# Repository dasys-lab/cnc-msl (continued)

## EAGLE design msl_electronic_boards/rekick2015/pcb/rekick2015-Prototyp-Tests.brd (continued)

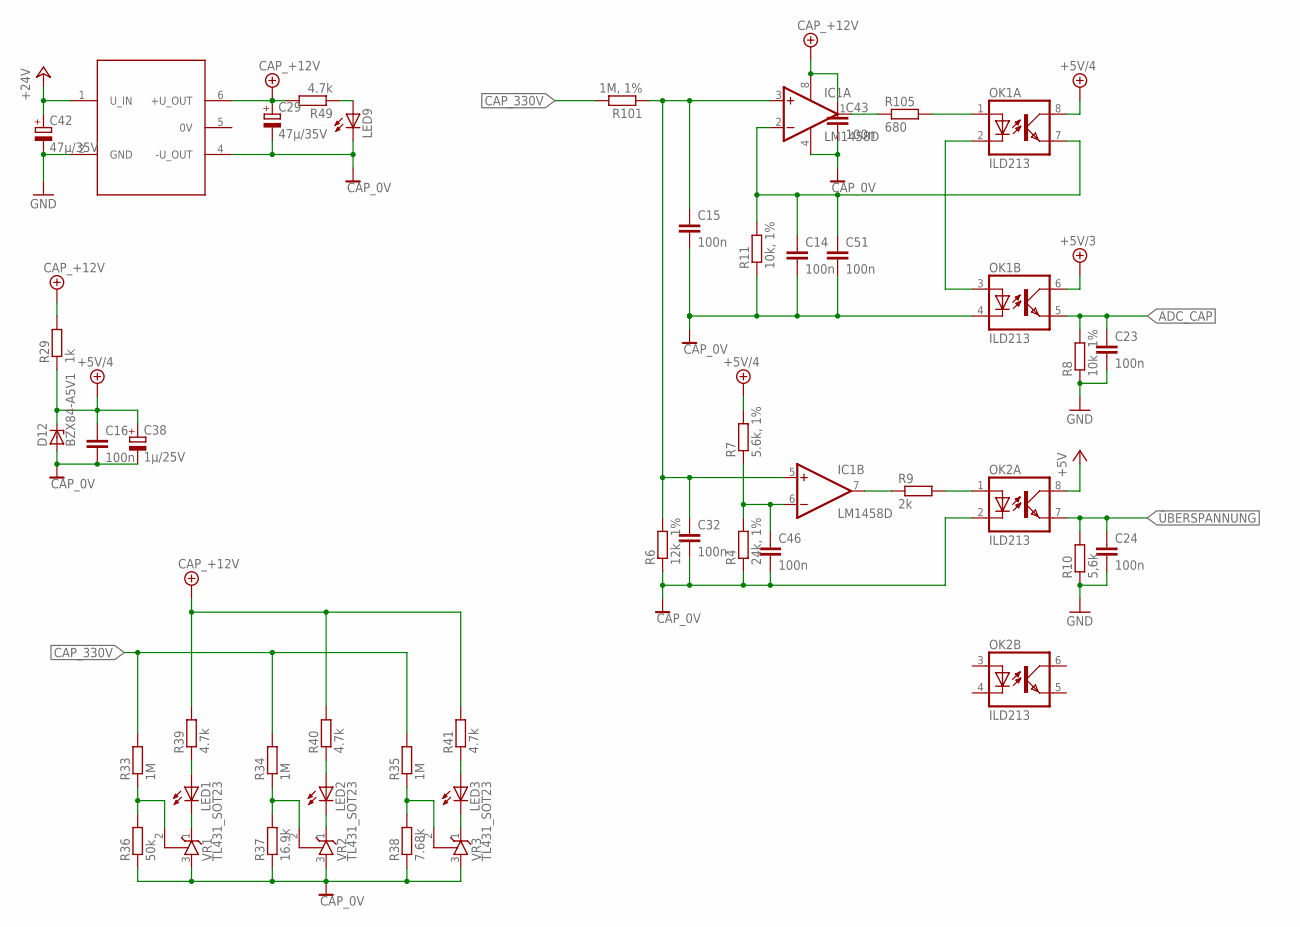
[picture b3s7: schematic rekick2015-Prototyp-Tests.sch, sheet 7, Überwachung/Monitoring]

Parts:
C14, C15, C16, C23, C24, C32, C43, C46, C51: 100n; C0603
C29, C42: 47µ/35V; PANASONIC_D
C38: 1µ/25V; SMC_A
D12: BZX84-A5V1; TO236
IC1: LM1458D; SO08
LED1, LED2, LED3, LED9: LEDCHIP-LED0805; CHIP-LED0805
OK1, OK2: ILD213; SOIC08
R4: 24k, 1%; R0805
R6: 12k, 1%; R0805
R7: 5.6k, 1%; R0805
R8, R11: 10k, 1%; R0805
R9: 2k; R0805
R10: 5,6k; R0805
R29: 1k; R0805
R33, R34, R35: 1M; R2512
R36: 50k; R0805
R37: 16.9k; R0805
R38: 7.68k; R0805
R39, R40, R41, R49: 4.7k; R0805
R101: 1M, 1%; R2512
R105: 680; R0805
U$4: TMH-D
VR1, VR2, VR3: TL431_SOT23; SOT23

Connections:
+5V: OK2.8 (COL); also elsewhere on the board
+5V/3: OK1.6 (COL); also elsewhere on the board
+5V/4: C16.1, C38.+, D12.C, OK1.8 (COL), R7.2, R29.1
+24V: C42.+, U$4.1 (U_IN); also elsewhere on the board
ADC_CAP: C23.1, OK1.5 (EMIT), R8.2; also elsewhere on the board
CAP_0V: C14.2, C15.2, C16.2, C29.-, C32.2, C38.-, C43.2, C46.2, C51.2, D12.A, IC1.4 (V-), LED9.C, OK1.4 (C), OK2.2 (C), R4.1, R6.1, R11.1, R36.1, R37.1, R38.1, U$4.4 (-U_OUT), VR1.3 (A), VR2.3 (A), VR3.3 (A); also elsewhere on the board
CAP_330V: R33.2, R34.2, R35.2, R101.2; also elsewhere on the board
CAP_+12V: C29.+, C43.1, IC1.8 (V+), R29.2, R39.2, R40.2, R41.2, R49.2, U$4.6 (+U_OUT); also elsewhere on the board
GND: C23.2, C24.2, C42.-, R8.1, R10.1, U$4.2 (GND); also elsewhere on the board
unnamed: LED1.C, VR1.1 (C)
unnamed: R33.1, R36.2, VR1.2 (R)
unnamed: IC1.1 (OUT), R105.1
unnamed: C14.1, C51.1, IC1.2 (-IN), OK1.7 (EMIT), R11.2
unnamed: C15.1, C32.1, IC1.3 (+IN), IC1.5 (+IN), R6.2, R101.1
unnamed: OK1.1 (A), R105.2
unnamed: OK1.2 (C), OK1.3 (A)
unnamed: IC1.7 (OUT), R9.1
unnamed: C46.1, IC1.6 (-IN), R4.2, R7.1
unnamed: OK2.1 (A), R9.2
unnamed: R34.1, R37.2, VR2.2 (R)
unnamed: R35.1, R38.2, VR3.2 (R)
unnamed: LED2.C, VR2.1 (C)
unnamed: LED3.C, VR3.1 (C)
unnamed: LED1.A, R39.1
unnamed: LED2.A, R40.1
unnamed: LED3.A, R41.1
unnamed: LED9.A, R49.1
ÜBERSPANNUNG: C24.1, OK2.7 (EMIT), R10.2; also elsewhere on the board

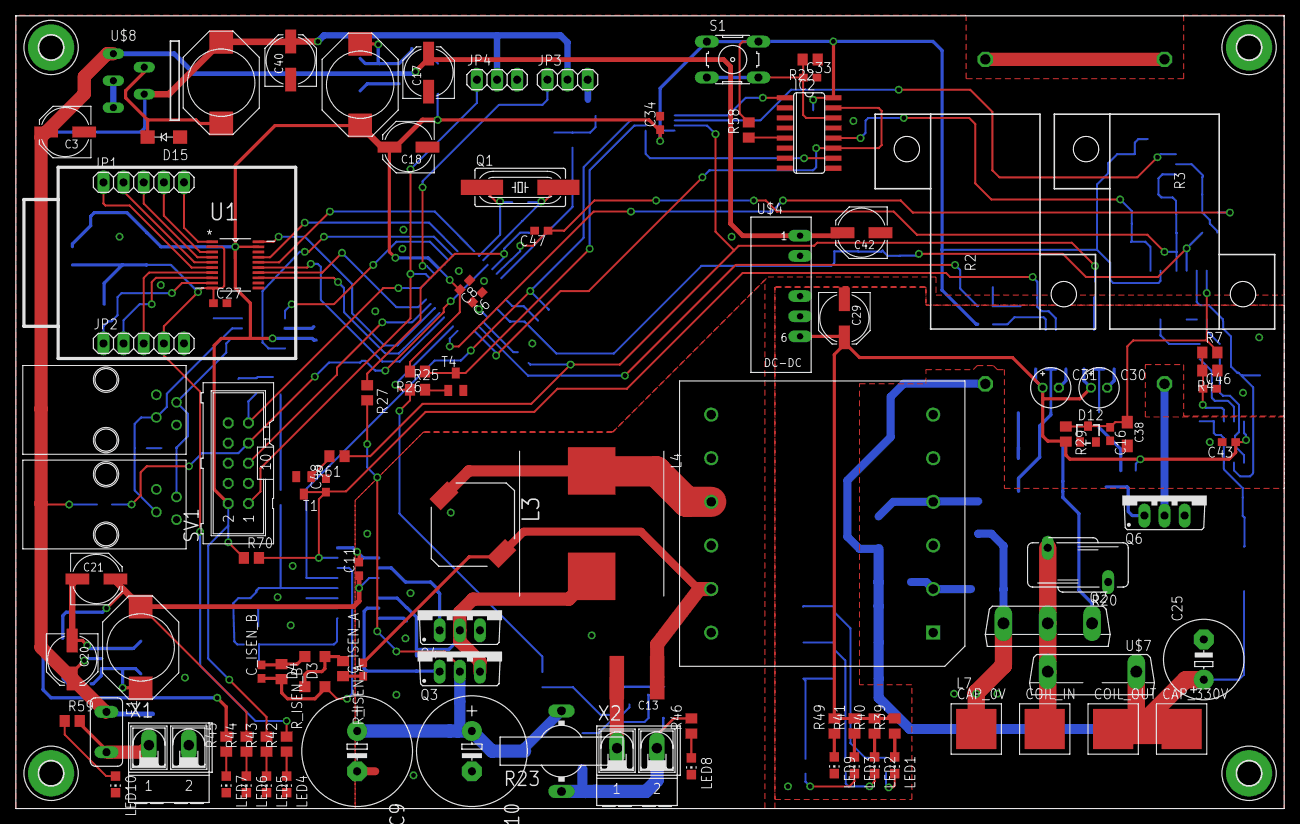
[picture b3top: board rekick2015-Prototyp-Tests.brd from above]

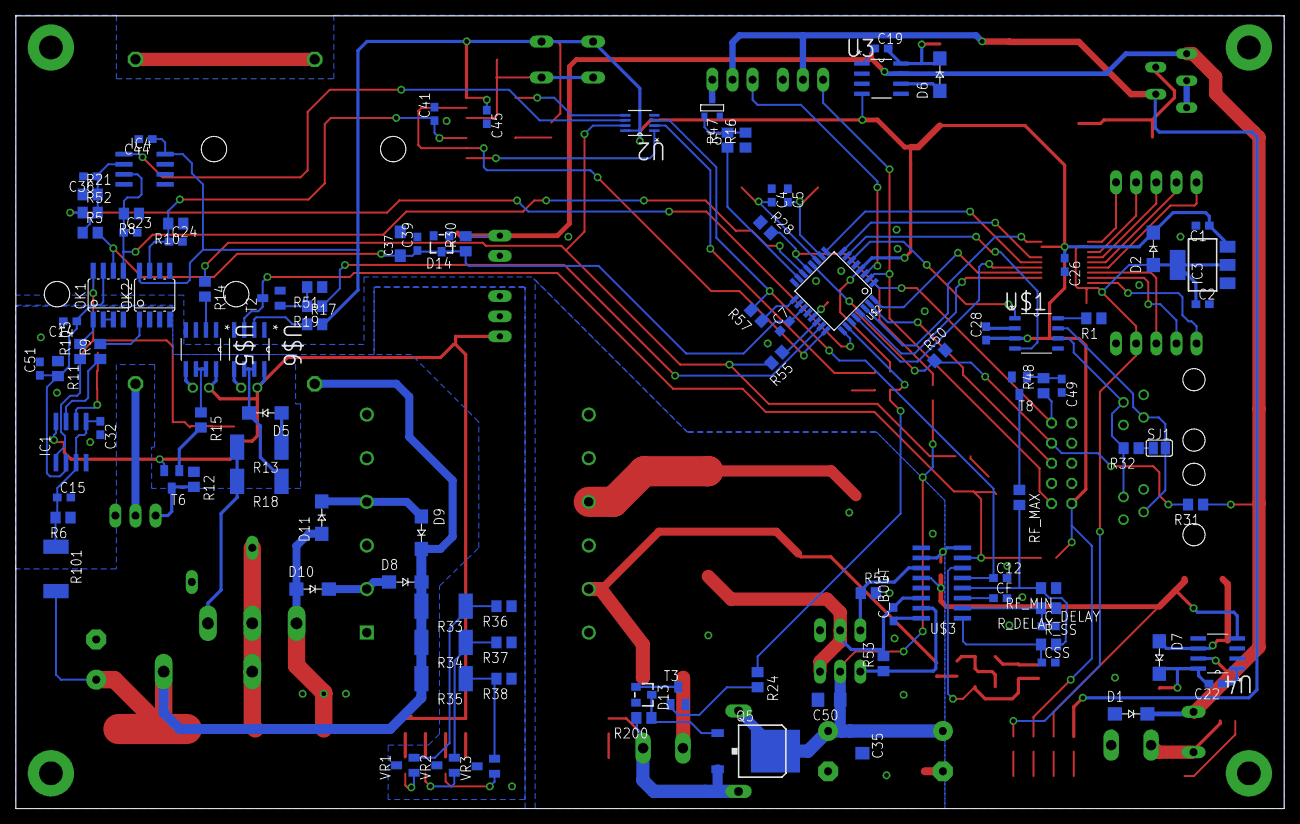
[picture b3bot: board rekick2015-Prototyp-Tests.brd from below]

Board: 2 copper layers, 160.0 x 100.0 mm, 211 parts (106 on the bottom side), 128 nets.

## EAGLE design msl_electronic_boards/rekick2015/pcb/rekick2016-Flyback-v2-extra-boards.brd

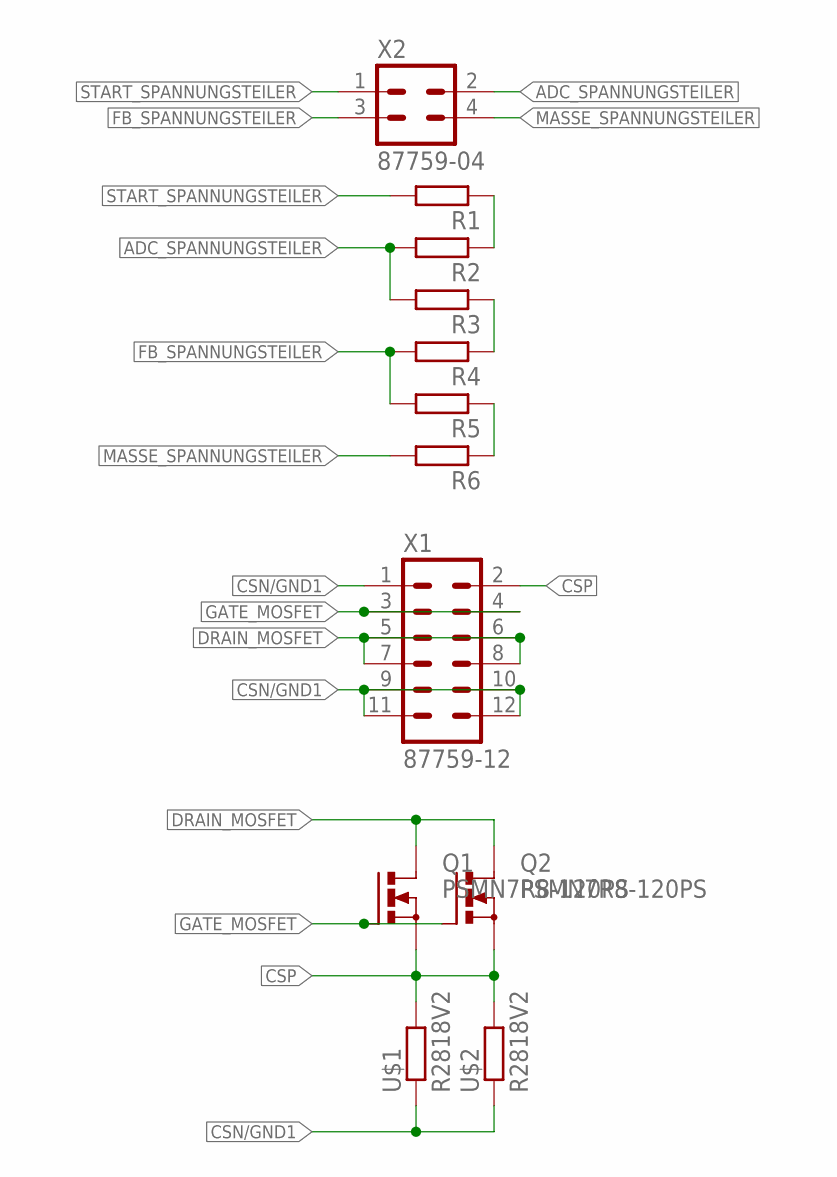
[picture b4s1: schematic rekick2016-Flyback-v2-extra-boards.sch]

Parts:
Q1, Q2: PSMN7R8-120PS; TO220BV
R1, R2, R3, R4, R5, R6: R-EU_R0805; R0805
U$1, U$2: R2818V2; R2818
X1: 87759-12
X2: 87759-04

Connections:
ADC_SPANNUNGSTEILER: R2.2, R3.2, X2.2
CSN/GND1: U$1.1, U$2.1, X1.1, X1.9, X1.10, X1.11, X1.12
CSP: Q1.S, Q2.S, U$1.2, U$2.2, X1.2
DRAIN_MOSFET: Q1.D, Q2.D, X1.5, X1.6, X1.7, X1.8
FB_SPANNUNGSTEILER: R4.2, R5.2, X2.3
GATE_MOSFET: Q1.G, Q2.G, X1.3, X1.4
MASSE_SPANNUNGSTEILER: R6.2, X2.4
unnamed: R1.1, R2.1
unnamed: R3.1, R4.1
unnamed: R5.1, R6.1
START_SPANNUNGSTEILER: R1.2, X2.1

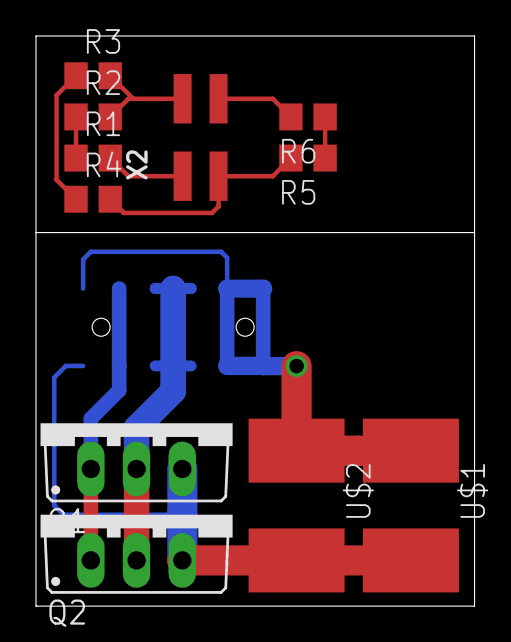
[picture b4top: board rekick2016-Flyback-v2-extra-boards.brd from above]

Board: 2 copper layers, 24.4 x 31.7 mm, 12 parts (1 on the bottom side), 11 nets.

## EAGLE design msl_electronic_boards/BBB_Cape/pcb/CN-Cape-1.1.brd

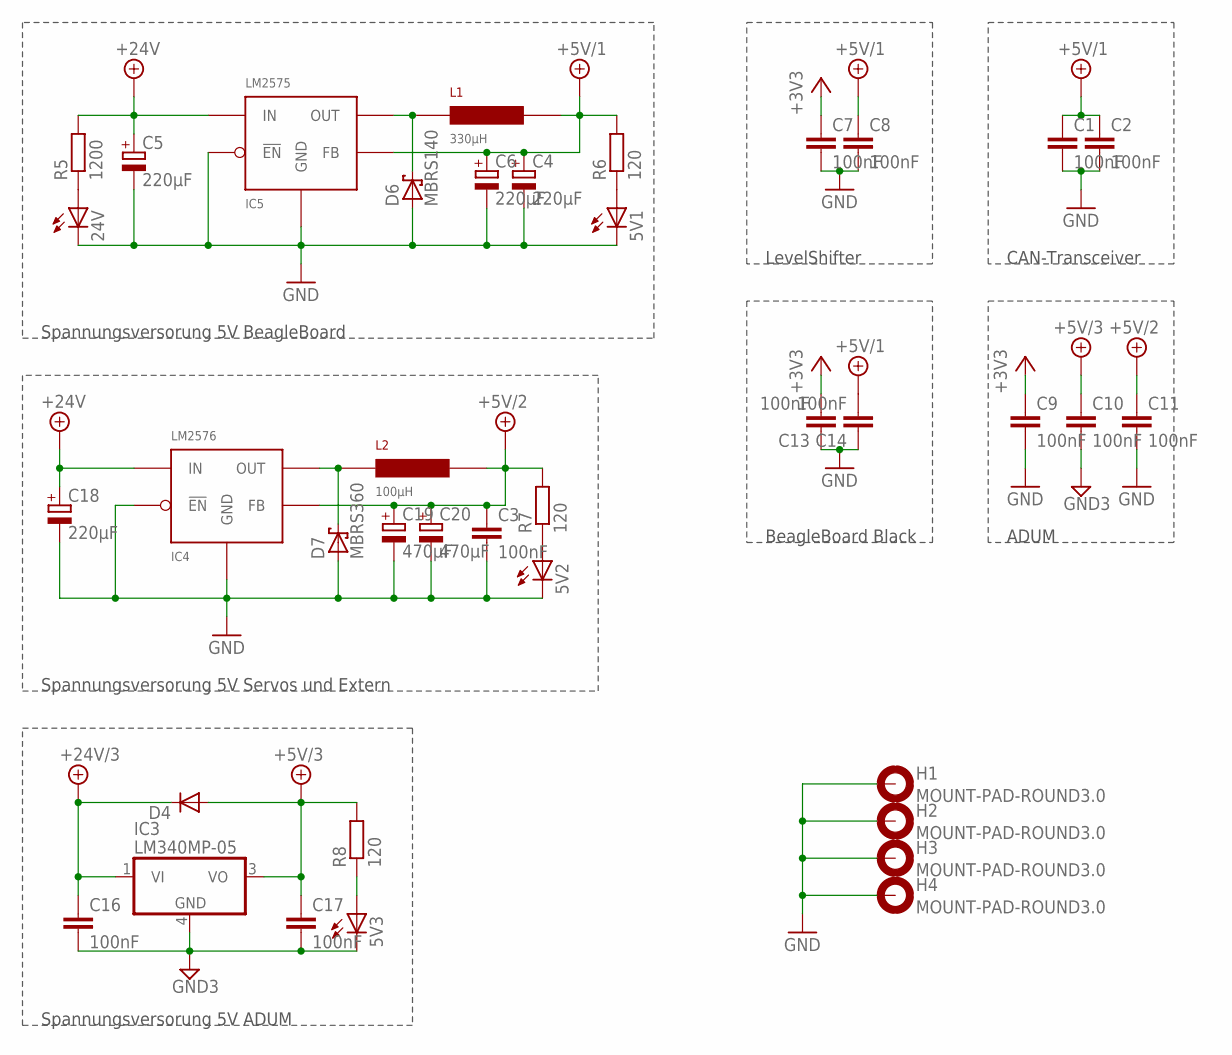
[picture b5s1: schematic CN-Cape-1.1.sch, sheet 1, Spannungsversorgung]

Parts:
5V1, 5V2, 5V3, 24V: LEDCHIP-LED0603; CHIP-LED0603
C1, C2, C3, C7, C8, C9, C10, C11, C13, C14, C16, C17: 100nF; C0603
C4, C6: 220µF; E2,5-6
C5, C18: 220µF; E3,5-8
C19, C20: 470µF; E3,5-8
D4: DIODE-SOD123; SOD123
D6: MBRS140; SMB
D7: MBRS360; SMC
H1, H2, H3, H4: MOUNT-PAD-ROUND3.0; 3,0-PAD
IC3: LM340MP-05; SOT223
IC4: LM2576; TO220-5_STAGGERED
IC5: LM2575; TO220-5_STAGGERED
L1: 330µH; PISR
L2: 100µH; PISR
R5: 1200; R0805
R6, R7, R8: 120; R0805

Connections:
+3V3: C7.1, C9.1, C13.2; also elsewhere on the board
+5V/1: C1.1, C2.1, C4.+, C6.+, C8.1, C14.2, IC5.FB, L1.P$2, R6.2; also elsewhere on the board
+5V/2: C3.1, C11.1, C19.+, C20.+, IC4.FB, L2.P$2, R7.2; also elsewhere on the board
+5V/3: C10.1, C17.1, D4.A, IC3.3 (VO), R8.2; also elsewhere on the board
+24V: C5.+, C18.+, IC4.IN, IC5.IN, R5.2; also elsewhere on the board
+24V/3: C16.1, D4.C, IC3.1 (VI); also elsewhere on the board
GND: 5V1.C, 5V2.C, 24V.C, C1.2, C2.2, C3.2, C4.-, C5.-, C6.-, C7.2, C8.2, C9.2, C11.2, C13.1, C14.1, C18.-, C19.-, C20.-, D6.A, D7.A, H1.B3,0, H2.B3,0, H3.B3,0, H4.B3,0, IC4.!EN, IC4.GND, IC5.!EN, IC5.GND; also elsewhere on the board
GND3: 5V3.C, C10.2, C16.2, C17.2, IC3.4 (GND); also elsewhere on the board
unnamed: 24V.A, R5.1
unnamed: 5V1.A, R6.1
unnamed: 5V2.A, R7.1
unnamed: D6.C, IC5.OUT, L1.P$1
unnamed: D7.C, IC4.OUT, L2.P$1
unnamed: 5V3.A, R8.1

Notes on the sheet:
LevelShifter
CAN-Transceiver
BeagleBoard Black
Spannungsversorung 5V BeagleBoard
Spannungsversorung 5V Servos und Extern
Spannungsversorung 5V ADUM
ADUM

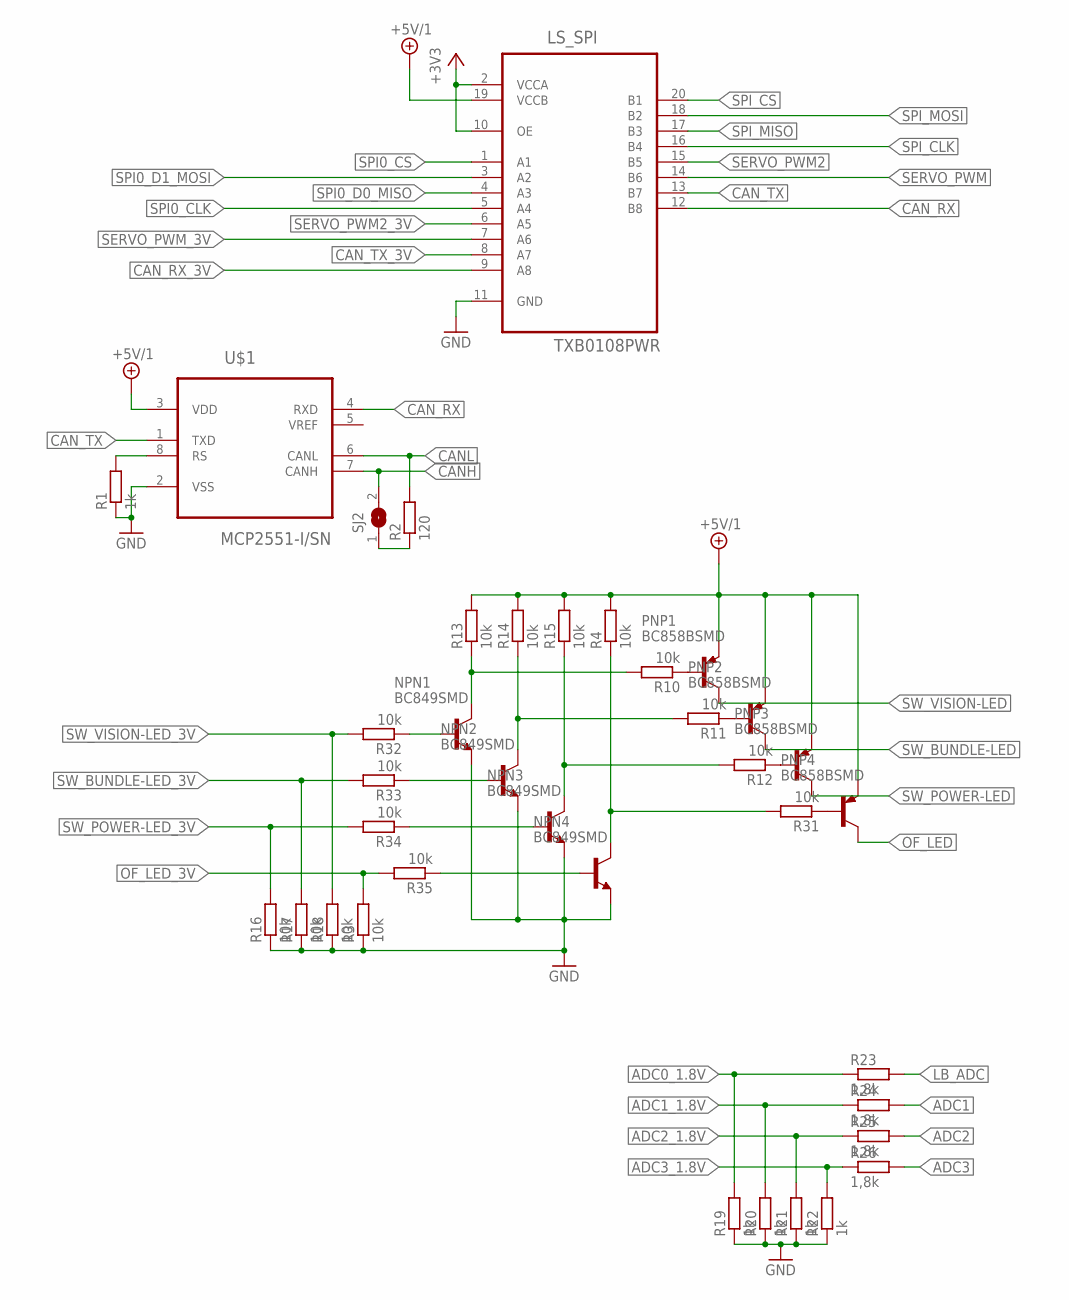
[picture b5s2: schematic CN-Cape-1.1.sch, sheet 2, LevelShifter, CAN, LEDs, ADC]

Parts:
LS_SPI: TXB0108PWR; SOP65P640X120-20N
NPN1, NPN2, NPN3, NPN4: BC849SMD; SOT23-BEC
PNP1, PNP2, PNP3, PNP4: BC858BSMD; SOT23-BEC
R1, R19, R20, R21, R22: 1k; R0805
R2: 120; R0805
R3, R4, R10, R11, R12, R13, R14, R15, R16, R17, R18, R31, R32, R33, R34, R35: 10k; R0805
R23, R24, R25, R26: 1,8k; R0805
SJ2: SJ
U$1: MCP2551-I/SN; SOIC127P600X175-8N

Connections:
+3V3: LS_SPI.2 (VCCA), LS_SPI.10 (OE); also elsewhere on the board
+5V/1: LS_SPI.19 (VCCB), PNP1.E, PNP2.E, PNP3.E, PNP4.E, R4.2, R13.2, R14.2, R15.2, U$1.3 (VDD); also elsewhere on the board
ADC0_1.8V: R19.2, R23.1; also elsewhere on the board
ADC1: R24.2; also elsewhere on the board
ADC1_1.8V: R20.2, R24.1; also elsewhere on the board
ADC2: R25.2; also elsewhere on the board
ADC2_1.8V: R21.2, R25.1; also elsewhere on the board
ADC3: R26.2; also elsewhere on the board
ADC3_1.8V: R22.2, R26.1; also elsewhere on the board
CANH: SJ2.2, U$1.7 (CANH); also elsewhere on the board
CANL: R2.2, U$1.6 (CANL); also elsewhere on the board
CAN_RX: LS_SPI.12 (B8), U$1.4 (RXD)
CAN_RX_3V: LS_SPI.9 (A8); also elsewhere on the board
CAN_TX: LS_SPI.13 (B7), U$1.1 (TXD)
CAN_TX_3V: LS_SPI.8 (A7); also elsewhere on the board
GND: LS_SPI.11 (GND), NPN1.E, NPN2.E, NPN3.E, NPN4.E, R1.1, R3.1, R16.1, R17.1, R18.1, R19.1, R20.1, R21.1, R22.1, U$1.2 (VSS); also elsewhere on the board
LB_ADC: R23.2; also elsewhere on the board
unnamed: NPN1.C, R10.2, R13.1
unnamed: NPN2.C, R11.2, R14.1
unnamed: NPN4.C, R4.1, R31.2
unnamed: NPN3.C, R12.2, R15.1
unnamed: R1.2, U$1.8 (RS)
unnamed: R2.1, SJ2.1
unnamed: PNP1.B, R10.1
unnamed: PNP2.B, R11.1
unnamed: PNP3.B, R12.1
unnamed: PNP4.B, R31.1
unnamed: NPN1.B, R32.1
unnamed: NPN2.B, R33.1
unnamed: NPN3.B, R34.1
unnamed: NPN4.B, R35.1
OF_LED: PNP4.C; also elsewhere on the board
OF_LED_3V: R3.2, R35.2; also elsewhere on the board
SERVO_PWM: LS_SPI.14 (B6); also elsewhere on the board
SERVO_PWM2: LS_SPI.15 (B5); also elsewhere on the board
SERVO_PWM2_3V: LS_SPI.6 (A5); also elsewhere on the board
SERVO_PWM_3V: LS_SPI.7 (A6); also elsewhere on the board
SPI0_CLK: LS_SPI.5 (A4); also elsewhere on the board
SPI0_CS: LS_SPI.1 (A1); also elsewhere on the board
SPI0_D0_MISO: LS_SPI.4 (A3); also elsewhere on the board
SPI0_D1_MOSI: LS_SPI.3 (A2); also elsewhere on the board
SPI_CLK: LS_SPI.16 (B4); also elsewhere on the board
SPI_CS: LS_SPI.20 (B1); also elsewhere on the board
SPI_MISO: LS_SPI.17 (B3); also elsewhere on the board
SPI_MOSI: LS_SPI.18 (B2); also elsewhere on the board
SW_BUNDLE-LED: PNP2.C; also elsewhere on the board
SW_BUNDLE-LED_3V: R17.2, R33.2; also elsewhere on the board
SW_POWER-LED: PNP3.C; also elsewhere on the board
SW_POWER-LED_3V: R16.2, R34.2; also elsewhere on the board
SW_VISION-LED: PNP1.C; also elsewhere on the board
SW_VISION-LED_3V: R18.2, R32.2; also elsewhere on the board

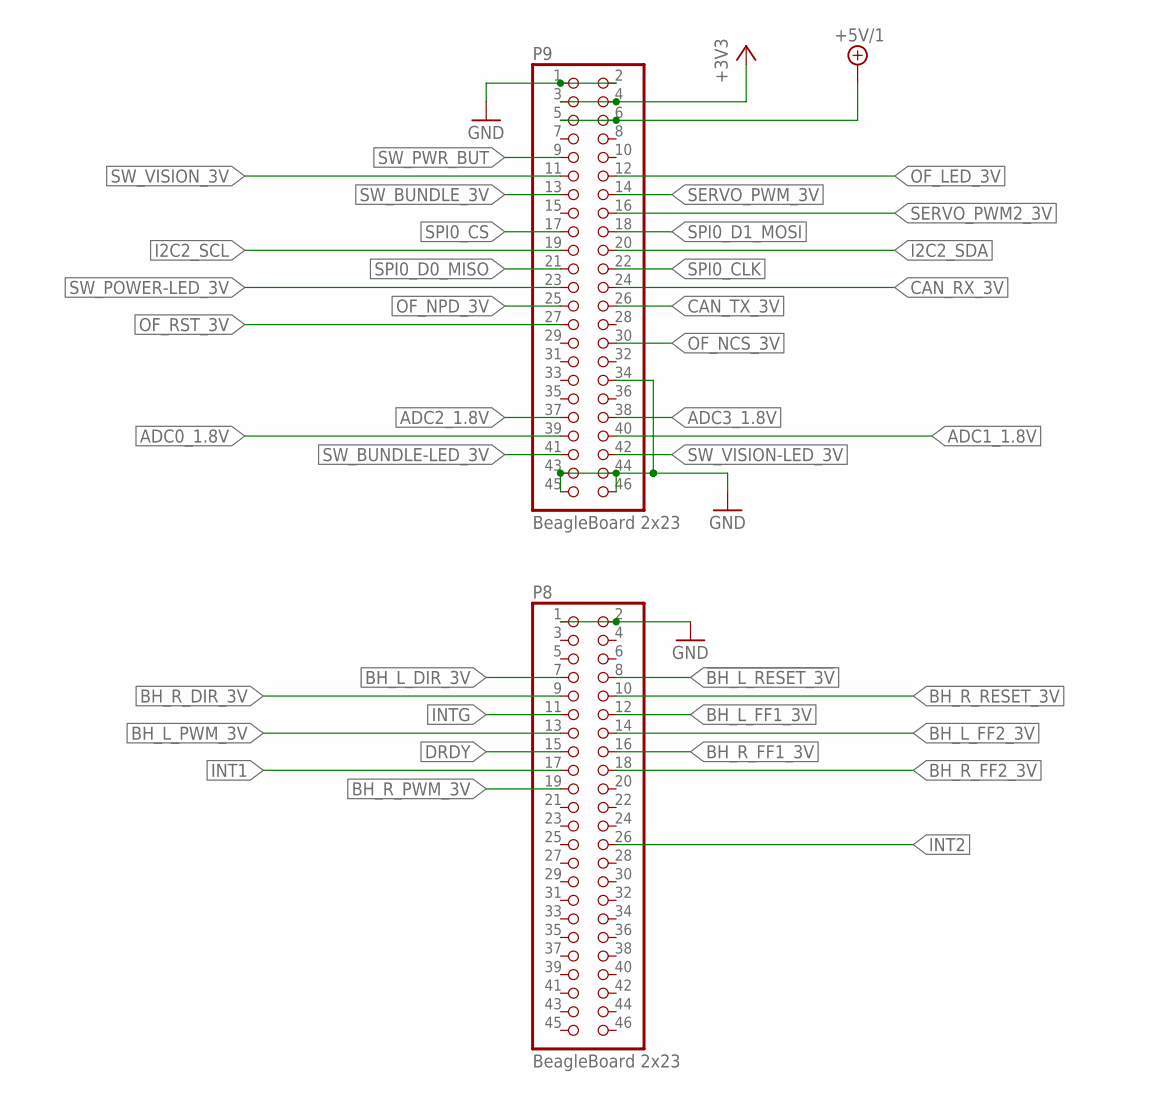
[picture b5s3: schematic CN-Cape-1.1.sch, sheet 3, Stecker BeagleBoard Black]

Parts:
P8, P9: BeagleBoard 2x23; 2X23

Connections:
!BH_L_RESET_3V: P8.8; also elsewhere on the board
!BH_R_RESET_3V: P8.10; also elsewhere on the board
+3V3: P9.3, P9.4; also elsewhere on the board
+5V/1: P9.5, P9.6; also elsewhere on the board
ADC0_1.8V: P9.39; also elsewhere on the board
ADC1_1.8V: P9.40; also elsewhere on the board
ADC2_1.8V: P9.37; also elsewhere on the board
ADC3_1.8V: P9.38; also elsewhere on the board
BH_L_DIR_3V: P8.7; also elsewhere on the board
BH_L_FF1_3V: P8.12; also elsewhere on the board
BH_L_FF2_3V: P8.14; also elsewhere on the board
BH_L_PWM_3V: P8.13; also elsewhere on the board
BH_R_DIR_3V: P8.9; also elsewhere on the board
BH_R_FF1_3V: P8.16; also elsewhere on the board
BH_R_FF2_3V: P8.18; also elsewhere on the board
BH_R_PWM_3V: P8.19; also elsewhere on the board
CAN_RX_3V: P9.24; also elsewhere on the board
CAN_TX_3V: P9.26; also elsewhere on the board
DRDY: P8.15; also elsewhere on the board
GND: P8.1, P8.2, P9.1, P9.2, P9.34, P9.43, P9.44, P9.45, P9.46; also elsewhere on the board
I2C2_SCL: P9.19; also elsewhere on the board
I2C2_SDA: P9.20; also elsewhere on the board
INT1: P8.17; also elsewhere on the board
INT2: P8.26; also elsewhere on the board
INTG: P8.11; also elsewhere on the board
OF_LED_3V: P9.12; also elsewhere on the board
OF_NCS_3V: P9.30; also elsewhere on the board
OF_NPD_3V: P9.25; also elsewhere on the board
OF_RST_3V: P9.27; also elsewhere on the board
SERVO_PWM2_3V: P9.16; also elsewhere on the board
SERVO_PWM_3V: P9.14; also elsewhere on the board
SPI0_CLK: P9.22; also elsewhere on the board
SPI0_CS: P9.17; also elsewhere on the board
SPI0_D0_MISO: P9.21; also elsewhere on the board
SPI0_D1_MOSI: P9.18; also elsewhere on the board
SW_BUNDLE-LED_3V: P9.41; also elsewhere on the board
SW_BUNDLE_3V: P9.13; also elsewhere on the board
SW_POWER-LED_3V: P9.23; also elsewhere on the board
SW_PWR_BUT: P9.9; also elsewhere on the board
SW_VISION-LED_3V: P9.42; also elsewhere on the board
SW_VISION_3V: P9.11; also elsewhere on the board

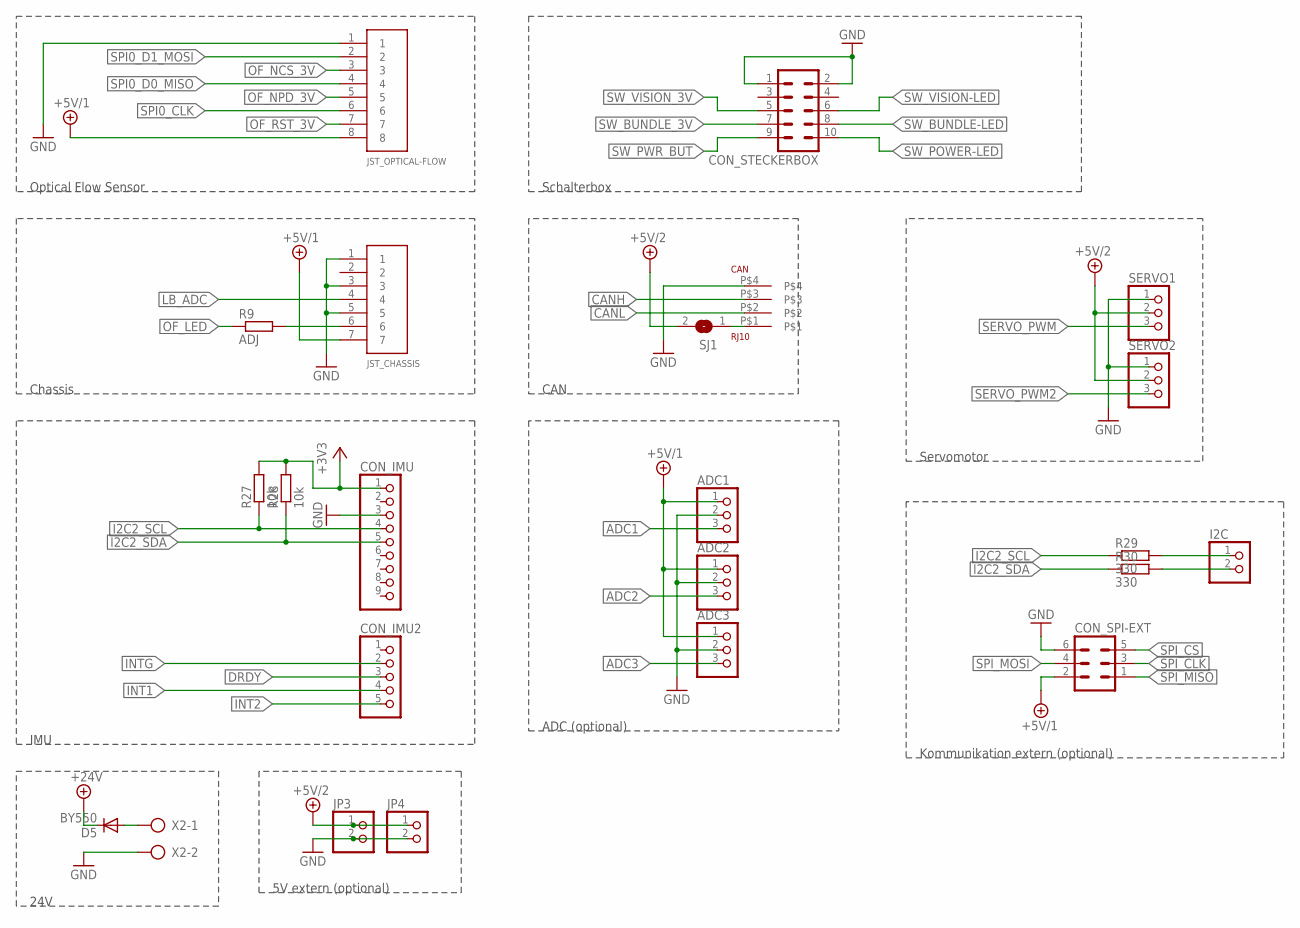
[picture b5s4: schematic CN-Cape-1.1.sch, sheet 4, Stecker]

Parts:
ADC1, ADC2, ADC3: PINHD-1X3; 1X03
CAN: RJ10
CON_IMU: PINHD-1X9; 1X09
CON_IMU2: PINHD-1X5; 1X05
CON_SPI-EXT: ML6
CON_STECKERBOX: ML10
D5: BY550; DO27-15
I2C: PINHD-1X2; 1X02
JP3, JP4: PINHD-1X2; 1X02
JST_CHASSIS: S7PIN; S7B-EH
JST_OPTICAL-FLOW: S8PIN; S8B-EH
R9: ADJ; R0805
R27, R28: 10k; R0805
R29, R30: 330; R0805
SERVO1, SERVO2: PINHD-1X3; 1X03
SJ1: SJ
X2: AK500/2-H

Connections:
+3V3: CON_IMU.1, R27.2, R28.2; also elsewhere on the board
+5V/1: ADC1.1, ADC2.1, ADC3.1, CON_SPI-EXT.2, JST_CHASSIS.7, JST_OPTICAL-FLOW.8; also elsewhere on the board
+5V/2: JP3.1, JP4.1, SERVO1.2, SERVO2.2, SJ1.2; also elsewhere on the board
+24V: D5.C; also elsewhere on the board
ADC1: ADC1.3; also elsewhere on the board
ADC2: ADC2.3; also elsewhere on the board
ADC3: ADC3.3; also elsewhere on the board
CANH: CAN.P$3; also elsewhere on the board
CANL: CAN.P$2; also elsewhere on the board
DRDY: CON_IMU2.3; also elsewhere on the board
GND: ADC1.2, ADC2.2, ADC3.2, CAN.P$4, CON_IMU.3, CON_SPI-EXT.6, CON_STECKERBOX.1, CON_STECKERBOX.2, JP3.2, JP4.2, JST_CHASSIS.1, JST_CHASSIS.3, JST_CHASSIS.5, JST_OPTICAL-FLOW.1, SERVO1.1, SERVO2.1, X2.2; also elsewhere on the board
I2C2_SCL: CON_IMU.4, R27.1, R29.1; also elsewhere on the board
I2C2_SDA: CON_IMU.5, R28.1, R30.1; also elsewhere on the board
INT1: CON_IMU2.4; also elsewhere on the board
INT2: CON_IMU2.5; also elsewhere on the board
INTG: CON_IMU2.2; also elsewhere on the board
LB_ADC: JST_CHASSIS.4; also elsewhere on the board
unnamed: D5.A, X2.1
unnamed: JST_CHASSIS.6, R9.2
unnamed: I2C.1, R29.2
unnamed: I2C.2, R30.2
unnamed: CAN.P$1, SJ1.1
OF_LED: R9.1; also elsewhere on the board
OF_NCS_3V: JST_OPTICAL-FLOW.3; also elsewhere on the board
OF_NPD_3V: JST_OPTICAL-FLOW.5; also elsewhere on the board
OF_RST_3V: JST_OPTICAL-FLOW.7; also elsewhere on the board
SERVO_PWM: SERVO1.3; also elsewhere on the board
SERVO_PWM2: SERVO2.3; also elsewhere on the board
SPI0_CLK: JST_OPTICAL-FLOW.6; also elsewhere on the board
SPI0_D0_MISO: JST_OPTICAL-FLOW.4; also elsewhere on the board
SPI0_D1_MOSI: JST_OPTICAL-FLOW.2; also elsewhere on the board
SPI_CLK: CON_SPI-EXT.3; also elsewhere on the board
SPI_CS: CON_SPI-EXT.5; also elsewhere on the board
SPI_MISO: CON_SPI-EXT.1; also elsewhere on the board
SPI_MOSI: CON_SPI-EXT.4; also elsewhere on the board
SW_BUNDLE-LED: CON_STECKERBOX.8; also elsewhere on the board
SW_BUNDLE_3V: CON_STECKERBOX.7; also elsewhere on the board
SW_POWER-LED: CON_STECKERBOX.10; also elsewhere on the board
SW_PWR_BUT: CON_STECKERBOX.9; also elsewhere on the board
SW_VISION-LED: CON_STECKERBOX.6; also elsewhere on the board
SW_VISION_3V: CON_STECKERBOX.5; also elsewhere on the board

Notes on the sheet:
Optical Flow Sensor
Chassis
IMU
24V
5V extern (optional)
ADC (optional)
Schalterbox
CAN
Servomotor
Kommunikation extern (optional)

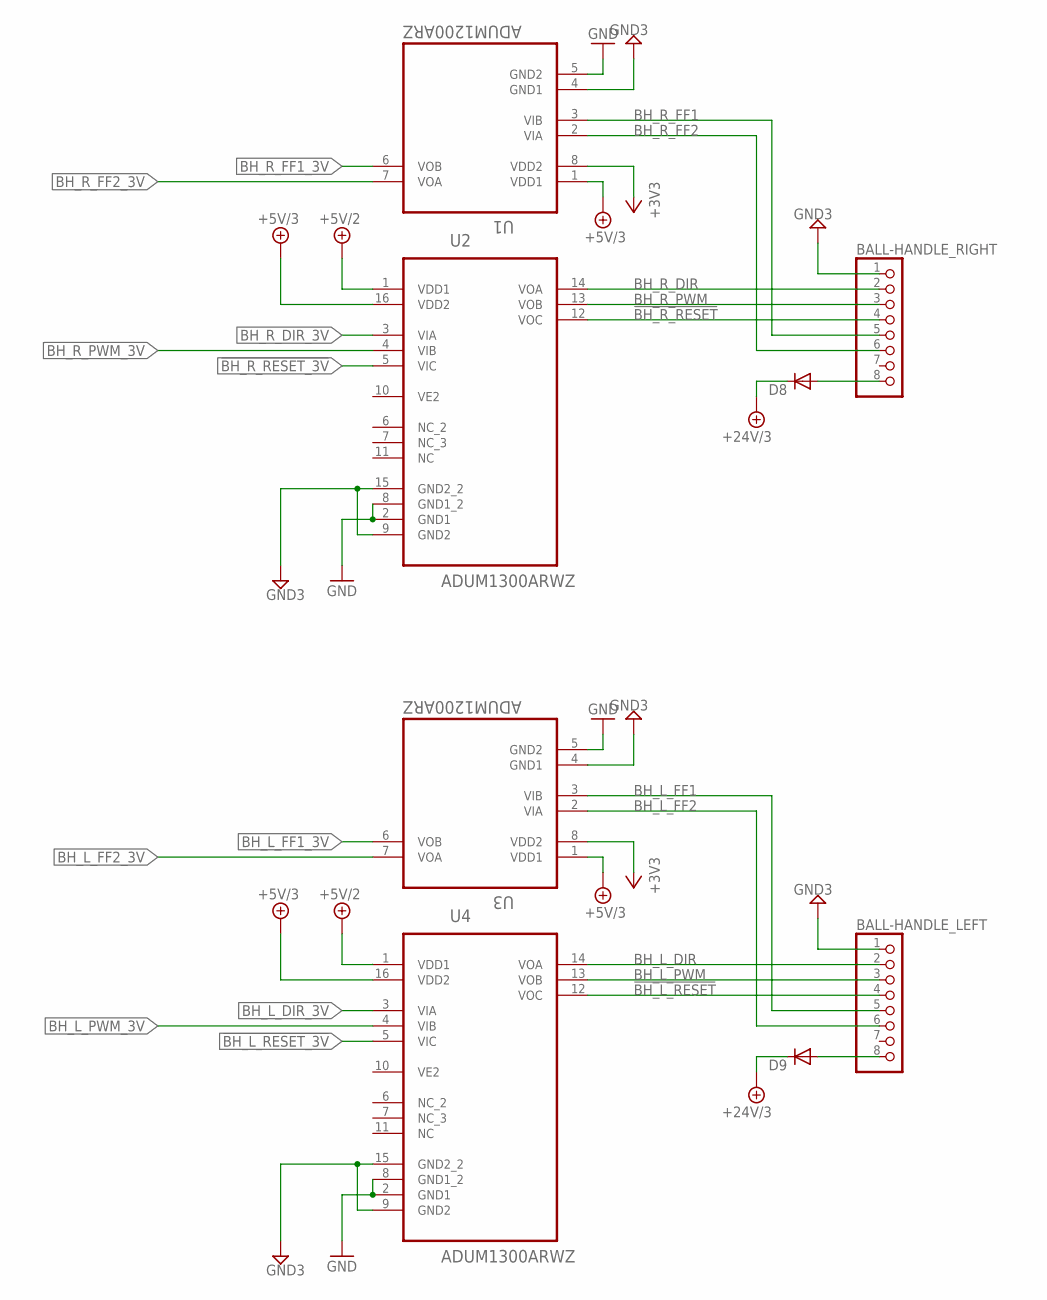
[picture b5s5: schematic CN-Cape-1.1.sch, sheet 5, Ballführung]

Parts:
BALL-HANDLE_LEFT: PINHD-1X8; 1X08
BALL-HANDLE_RIGHT: PINHD-1X8; 1X08
D8, D9: DIODE-SOD123; SOD123
U1, U3: ADUM1200ARZ; SOIC127P600X175-8N
U2, U4: ADUM1300ARWZ; SOIC127P1032X265-16N

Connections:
!BH_L_RESET: BALL-HANDLE_LEFT.4, U4.12 (VOC)
!BH_L_RESET_3V: U4.5 (VIC); also elsewhere on the board
!BH_R_RESET: BALL-HANDLE_RIGHT.4, U2.12 (VOC)
!BH_R_RESET_3V: U2.5 (VIC); also elsewhere on the board
+3V3: U1.8 (VDD2), U3.8 (VDD2); also elsewhere on the board
+5V/2: U2.1 (VDD1), U4.1 (VDD1); also elsewhere on the board
+5V/3: U1.1 (VDD1), U2.16 (VDD2), U3.1 (VDD1), U4.16 (VDD2); also elsewhere on the board
+24V/3: D8.C, D9.C; also elsewhere on the board
BH_L_DIR: BALL-HANDLE_LEFT.2, U4.14 (VOA)
BH_L_DIR_3V: U4.3 (VIA); also elsewhere on the board
BH_L_FF1: BALL-HANDLE_LEFT.5, U3.3 (VIB)
BH_L_FF1_3V: U3.6 (VOB); also elsewhere on the board
BH_L_FF2: BALL-HANDLE_LEFT.6, U3.2 (VIA)
BH_L_FF2_3V: U3.7 (VOA); also elsewhere on the board
BH_L_PWM: BALL-HANDLE_LEFT.3, U4.13 (VOB)
BH_L_PWM_3V: U4.4 (VIB); also elsewhere on the board
BH_R_DIR: BALL-HANDLE_RIGHT.2, U2.14 (VOA)
BH_R_DIR_3V: U2.3 (VIA); also elsewhere on the board
BH_R_FF1: BALL-HANDLE_RIGHT.5, U1.3 (VIB)
BH_R_FF1_3V: U1.6 (VOB); also elsewhere on the board
BH_R_FF2: BALL-HANDLE_RIGHT.6, U1.2 (VIA)
BH_R_FF2_3V: U1.7 (VOA); also elsewhere on the board
BH_R_PWM: BALL-HANDLE_RIGHT.3, U2.13 (VOB)
BH_R_PWM_3V: U2.4 (VIB); also elsewhere on the board
GND: U1.5 (GND2), U2.2 (GND1), U2.8 (GND1_2), U3.5 (GND2), U4.2 (GND1), U4.8 (GND1_2); also elsewhere on the board
GND3: BALL-HANDLE_LEFT.1, BALL-HANDLE_RIGHT.1, U1.4 (GND1), U2.9 (GND2), U2.15 (GND2_2), U3.4 (GND1), U4.9 (GND2), U4.15 (GND2_2); also elsewhere on the board
unnamed: BALL-HANDLE_LEFT.8, D9.A
unnamed: BALL-HANDLE_RIGHT.8, D8.A

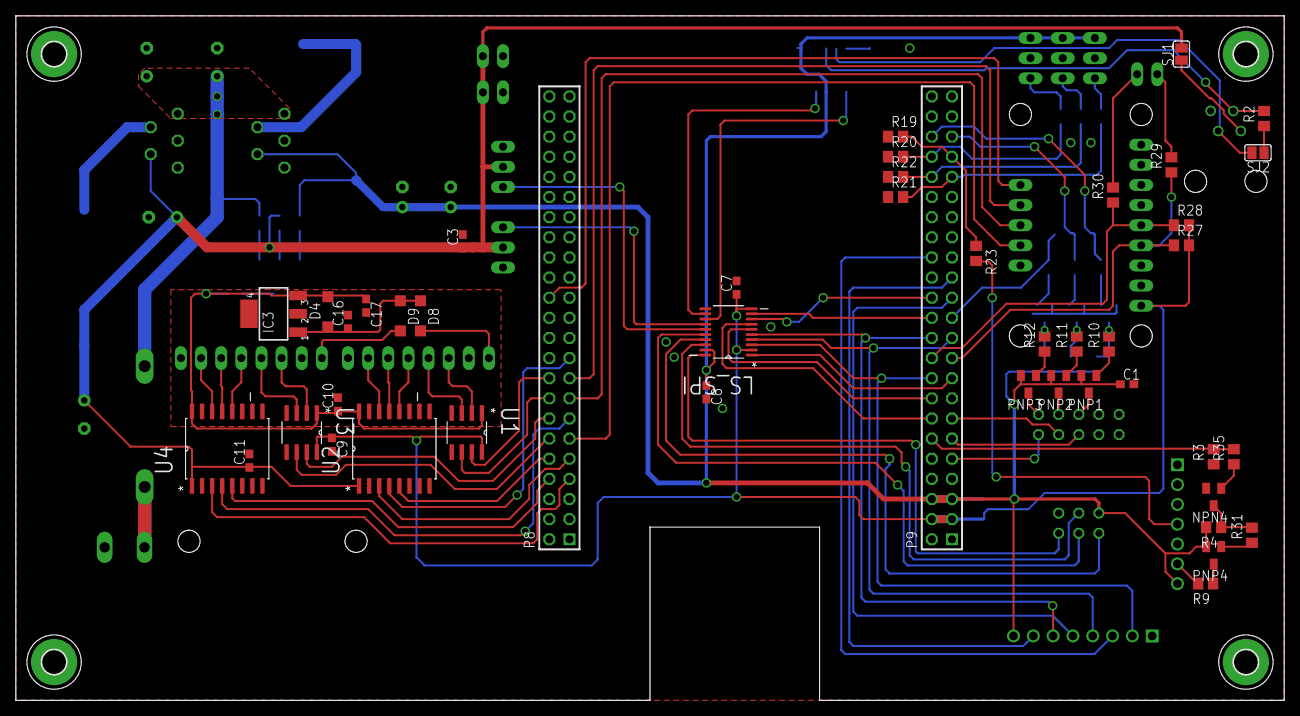
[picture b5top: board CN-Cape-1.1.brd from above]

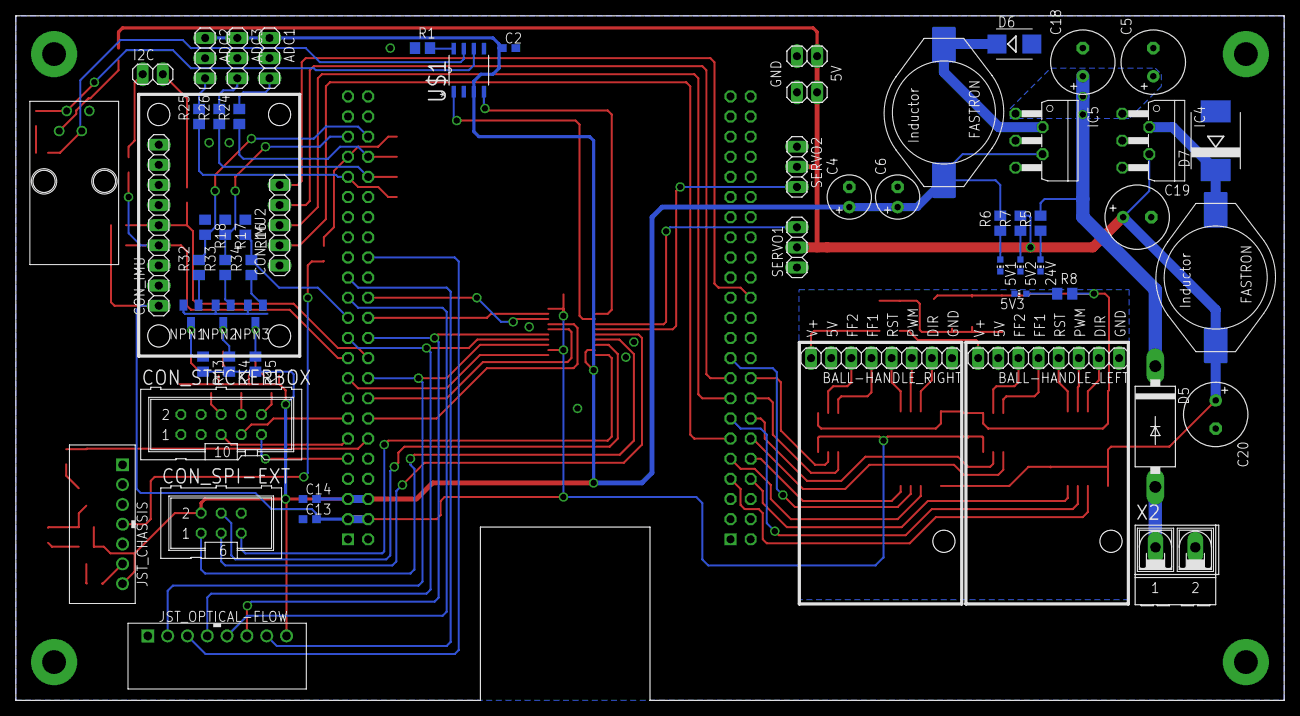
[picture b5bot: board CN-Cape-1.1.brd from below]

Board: 2 copper layers, 160.0 x 86.4 mm, 108 parts (59 on the bottom side), 101 nets.
